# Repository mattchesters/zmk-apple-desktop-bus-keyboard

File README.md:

# ⌨️ Apple Desktop Bus Keyboard modernization project

**This repository includes all the files used in the [mtt](https://www.youtube.com/@mttcx) YouTube video, _"[Apple's BEST keyboard... reimagined](https://www.youtube.com/watch?v=NW_LLVD3R3c)"_.**

<blockquote>
The 1986 Apple Desktop Bus Keyboard is a design marvel known for its enjoyable typing experience, but using it today requires some engineering. This modernization project introduces a custom PCB and development board to add Bluetooth connectivity using ZMK, a low-energy display for layer and device status, and a rotary encoder for volume control. 
</blockquote>

##

This README can be used as supporting information to the video. If you are undertaking this project yourself, please familiarize yourself with [ZMK firmware](https://zmk.dev), and the PCB design and schematic files.

## ⚠️ Disclaimer
The results will vary depending on the condition of your keyboard.  
While efforts have been made to create a functional project, variations in individual keyboard conditions may lead to unique issues.

## ✍️ Schematic & Design
The PCB was designed in KiCad 8.0.

The Schematic, Design, and component Footprints are included in the [KiCad project files](./assets/kicad). 

If you are working on this project, take the time to thoroughly review the design and schematic to understand PCB utilization.

## 🛒 Bill of Materials

| Description | Part | Quantity | Link |
|---|---|---|---|
| Development Board | Seeed Studio XIAO nRF52840 | 1 | [Seeed Studio](https://wiki.seeedstudio.com/XIAO_BLE/) |
| Display | nice!view | 1 | [nice!](https://nicekeyboards.com/nice-view) |
| Rotary encoder | EC11 | 1 | [Amazon](https://www.amazon.co.uk/gp/product/B08728PS6N/ref=ppx_yo_dt_b_search_asin_title?ie=UTF8&psc=1)
| USB Port | USB TYPE-C 6P | 1 | [LCSC Electronics](https://www.lcsc.com/product-detail/USB-Connectors_SHOU-HAN-TYPE-C-6P-QT073_C2681548.html/)|
| Display/Encoder receptacle | JST SM05B | 2 | [LCSC Electronics](https://www.lcsc.com/product-detail/Wire-To-Board-Connector_JST-SM05B-SRSS-TB-LF-SN_C136657.html)|
| Display/Encoder plug | JST SHR-05V-S-B | 2 | [See below](#display%20&amp;%20encoder%20cables)|
| Lithium Polymer Battery | 110mAh | 1 | [Cool Components](https://coolcomponents.co.uk/products/lithium-polymer-battery-110mah?_pos=1&_psq=110mw&_ss=e&_v=1.0)
| Battery Connector | JST S2B-PH | 1 | [LCSC Electronics](https://www.lcsc.com/product-detail/Wire-To-Board-Connector_JST-S2B-PH-K-S-GW_C157932.html)|
| 10k resistor | 10k 0805 | 4 | [LCSC Electronics](https://www.lcsc.com/product-detail/Chip-Resistor-Surface-Mount_UNI-ROYAL-Uniroyal-Elec-0805W8F1002T5E_C17414.html)|
| 5.1k resistor | 5.1k 0805 | 2 | [LCSC Electronics](https://www.lcsc.com/product-detail/Chip-Resistor-Surface-Mount_UNI-ROYAL-Uniroyal-Elec-0805W8F5101T5E_C27834.html)|
| Power switch | MINI MSK12CO2 | 1 | [LCSC Electronics](https://www.lcsc.com/product-detail/Slide-Switches_SHOU-HAN-MINI-MSK12CO2_C2681570.html)

## 🔌 Display & encoder cables
As the small JST connectors used to connect the PCB to the display and rotary encoder requires specialist crimping tools, I opted to have the two cables fabricated by [LCSC custom cables](https://www.lcsc.com/customcables/), to the following specification:

| LCSC Part | Manufacture Part | Quantity |
|---|---|---|
| C268102 | JST SHR-05V-S-B | 1 |
| C263995 | SSH-003T-P0.2-H | 5 |

* Cable: AWG 30
* Length: 300mm
* Side 1: JST Connector
* Side 2: Flat cut wires

## 🛍️ Ordering the PCB
For convenience, the Production files have been included in this repository. These can be used to order your own PCB from a prototyping company, such as JLCPCB or PCBWay.

Please be comfortable with the ordering and validation process, as each company is different and may have inaccuracies you are responsible for.

1. Upload the [./assets/pcb/production-packed.zip]() to a provider.
2. If using the Assembly services, make sure all components are correctly placed.

## 📸 Flashing the XIAO Dev Board with ZMK
If you want to modify the firmware, you can review the code in [./boards/shields/adbk]() following the guidance from [ZMK documentation](https://zmk.dev/docs/development/hardware-integration/new-shield).

I have added a release with the firmware I use daily.

1. Connect the XIAO to your computer.
2. Download the **adbk_fw.uf2** from the [Releases](https://github.com/mattchesters/zmk-apple-desktop-bus-keyboard/releases/).
3. Place the XIAO nRF52840 in [bootloader mode](https://wiki.seeedstudio.com/XIAO_BLE/).
4. Drag and drop the **adbk_fw.uf2** file to the **XIAO-SENSE** volume on your computer.

The board will automatically exit bootloader mode and is ready to use.

## 🧑‍🏭 Preparing the PCB
If you have ordered from a fabrication company with assembly services, the may only have to solder the XIAO nRF52840 and through-hole component.

Review the schematic and design files to understand how the components are placed on the PCB.

## 🪛 Preparing the Keyboard
To install the custom components, some parts need to be removed. The process is reversible, allowing the keyboard to be restored to its original state.

1. Flip over the keyboard and remove the 3x screws with a PH2 driver bit.
2. Holding the top of the keyboard, return it to the upright position, then remove the top casing by lifting it upwards.
3. Carefully remove the 20 pin DIP package by lifting each side with equal force.
4. Remove the board from the PCB, by lift the top, and then sliding it upwards.
5. Desolder and remove the ADB ports.
6. Store the ADB ports and 20-pin DIP package in anti-static packaging for preservation.

## 🖨️ 3D Printed parts
The following parts help facilitate the modifications. These are:
* [Power button with Display cutout](./assets/models/power-cap)
* [ADB Port with switch and USB-C cutout](./assets/models/usb)
* [ADB Port with EC11 cutout](./assets/models/encoder)
* [EC11 encoder knob]((./assets/models/encoder))

These files are provided in STEP and 3MF formats.  
STEP allows for accurate modification in CAD software.  
3MF is designed to be more accessible for 3D printing.

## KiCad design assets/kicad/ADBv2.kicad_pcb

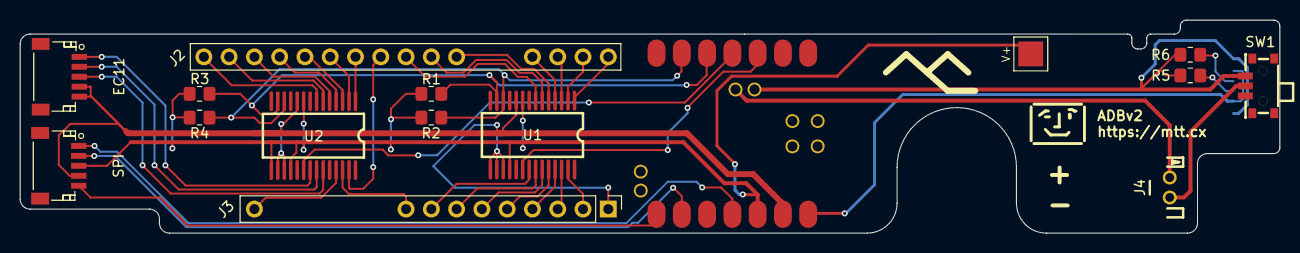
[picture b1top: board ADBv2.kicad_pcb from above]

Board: 2 copper layers, 126.6 x 21.4 mm, 17 parts (1 on the bottom side), 42 nets.

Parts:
EC11: EC11; CONN-SMD_SM05B-SRSS-TB-LF-SN
J2: TOP; PinHeader_1x20_P2.54mm_Vertical
J3: BOTTOM; PinHeader_1x20_P2.54mm_Vertical
J4: BAT; CONN-TH_S2B-PH-K-S-GW
R1, R2, R3, R4: 10k; R_0805_2012Metric_Pad1.20x1.40mm_HandSolder
R5, R6: 5.1k; R_0805_2012Metric_Pad1.20x1.40mm_HandSolder
SPI: SPI; CONN-SMD_SM05B-SRSS-TB-LF-SN
SW1: MINI MSK12CO2; SW-SMD_MSK12CO2
U1, U2: MCP23017-E/SS; SSOP-28_L10.2-W5.3-P0.65-LS7.8-BL
USB1: TYPE-C 6P QT073; USB-C-SMD_TYPE-C-6P-QT073
V+: 3.3v; TestPoint_Pad_3.0x3.0mm
XIAO1: MOUDLE-SEEEDUINO-XIAO-NRF52840; xiao-ble-smd

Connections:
CS: SPI.5, XIAO1.8 (B9_RX/1.12)
GND: EC11.4, EC11.5, J3.1 (GROUND), SPI.4, U1.10 (VSS), U1.15 (A0), U1.16 (A1), U1.17 (A2), U2.10 (VSS), U2.16 (A1), U2.17 (A2), XIAO1.13 (GND)
MOSI: SPI.1, XIAO1.11 (A6_MOSI/1.15)
unnamed: J2.4 (COMMAND), U1.4 (GPB3)
unnamed: J2.16 (CONTROL), U2.6 (GPB5)
unnamed: J2.3 (OPTION), U1.3 (GPB2)
unnamed: J2.15 (POWER), U2.5 (GPB4)
unnamed: J2.11 (R0), U2.1 (GPB0)
unnamed: J2.2 (R1), U1.2 (GPB1)
unnamed: J2.1 (R2), U1.1 (GPB0)
unnamed: J2.13 (R3), U2.3 (GPB2)
unnamed: J2.7 (R4), U1.5 (GPB4)
unnamed: J2.8 (R5), U1.6 (GPB5)
unnamed: J2.9 (R6), U1.7 (GPB6)
unnamed: J2.10 (R7), U2.27 (GPA6)
unnamed: J2.12 (R8), U2.2 (GPB1)
unnamed: J2.14 (R9), U2.4 (GPB3)
unnamed: J2.17 (SHIFT), U2.7 (GPB6)
unnamed: J3.2 (C0), U1.27 (GPA6)
unnamed: J3.3 (C1), U1.26 (GPA5)
unnamed: J3.4 (C2), U1.25 (GPA4)
unnamed: J3.5 (C3), U1.24 (GPA3)
unnamed: J3.6 (C4), U1.23 (GPA2)
unnamed: J3.7 (C5), U1.22 (GPA1)
unnamed: J3.8 (C6), U1.21 (GPA0)
unnamed: J3.9 (C7), U2.26 (GPA5)
unnamed: J3.15 (CAPSLOCK), U2.25 (GPA4)
unnamed: J4.1, XIAO1.19 (BAT)
unnamed: J4.2, SW1.2
unnamed: R5.2, R6.1, SW1.3, USB1.A12 (GND), USB1.B12 (GND), XIAO1.20 (GND)
unnamed: U1.20 (INTA), XIAO1.3 (A10/0.28)
unnamed: R2.1, R4.1, U1.12 (SCK), U2.12 (SCK), XIAO1.6 (A9_SCL/0.05_H)
unnamed: R1.1, R3.1, U1.13 (SDA), U2.13 (SDA), XIAO1.5 (A8_SDA/0.04_H)
unnamed: EC11.1, U2.21 (GPA0)
unnamed: EC11.2, U2.22 (GPA1)
unnamed: EC11.3, U2.23 (GPA2)
unnamed: U2.20 (INTA), XIAO1.4 (A11/0.29)
unnamed: R6.2, USB1.A5 (CC1)
unnamed: R5.1, USB1.B5 (CC2)
unnamed: USB1.A9 (VBUS), USB1.B9 (VBUS), XIAO1.14 (5V)
SCK: SPI.2, XIAO1.9 (A7_SCK/1.13)
VCC: R1.2, R2.2, R3.2, R4.2, SPI.3, U1.9 (VDD), U1.18 (~RESET), U2.9 (VDD), U2.15 (A0), U2.18 (~RESET), V+.1, XIAO1.12 (3V3)

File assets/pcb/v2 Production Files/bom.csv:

Designator,Footprint,Quantity,Value,LCSC Part #
EC11,CONN-SMD_SM05B-SRSS-TB-LF-SN,1,EC11,C265419
J4,CONN-TH_S2B-PH-K-S-GW,1,BAT,
"R1, R2, R3, R4",0805,4,10k,
"R5, R6",0805,2,5.1k,
SPI,CONN-SMD_SM05B-SRSS-TB-LF-SN,1,SPI,C265419
SW1,SW-SMD_MSK12CO2,1,MINI MSK12CO2,C2681570
"U1, U2",SSOP-28_L10.2-W5.3-P0.65-LS7.8-BL,2,MCP23017-E/SS,C506653
USB1,USB-C-SMD_TYPE-C-6P-QT073,1,TYPE-C 6P QT073,C2681548

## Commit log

2024-07-30 adds basic board requirements
2024-07-31 adds keymap
2024-07-31 adds build file
2024-07-31 copies keymap to config dir
2024-07-31 tidies keymap and overlay
2024-07-31 adds non-logging build
2024-08-02 makes all keys functioning
2024-08-20 board change to seeduino
    first functional build for seeduino.
    retires nice_nano
2024-08-26 adds soft_off functionality
2024-08-26 fixes hold-tap behavior
2024-09-12 enables ble while charing
2024-09-23 adds assets
2024-09-23 adds 3d model assets
2024-09-30 LICENSE
2024-10-08 adds capslock layer
    changes capslock behaviours to toggle a layers which activates keys with right shift modifier
2024-10-08 adds macro
    changes behaviour from RS to marco which toggles capslock each kp
2024-10-08 sets caps via RS
    uses RS modifier in caps lock layer. corrects key layout. improves encoder indents.
2024-10-08 fixes missing ampersand
2024-11-09 adds readme, kicad project
    restructures some directories
